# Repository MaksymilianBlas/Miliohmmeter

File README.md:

# Miliohmmeter
Miliohmmeter project, inspired by video on Learn Electronics Repair channel.
This is an adaptation of a project that has been shown on Learn Electronics Repair channel, link to original video:
https://www.youtube.com/watch?v=Sz1CqJltWEY
I wanted to replace the bulky PCB (that was designed by someone and posted on PCBway projects page) with my own design, with SMD parts and better layout. The project was made in KiCad.
Additionally, a linear power supply has been integrated onto the PCB.
The PCBA with a suitable transformer has been placed in a small project case, with banana sockets and a 5-digit display.
Along the way, there have been some issues caused by counterfit OP07 op-amps from aliexpress.
The weakpoint of the project are the home-made poor-mans kelvin connection probes, because the tip is soldered together and is neither sharp enough or resistant to oxidation enough to guarantee a long problem-free and pleasant usage. The leads were not updated due to high cost and lost interest.

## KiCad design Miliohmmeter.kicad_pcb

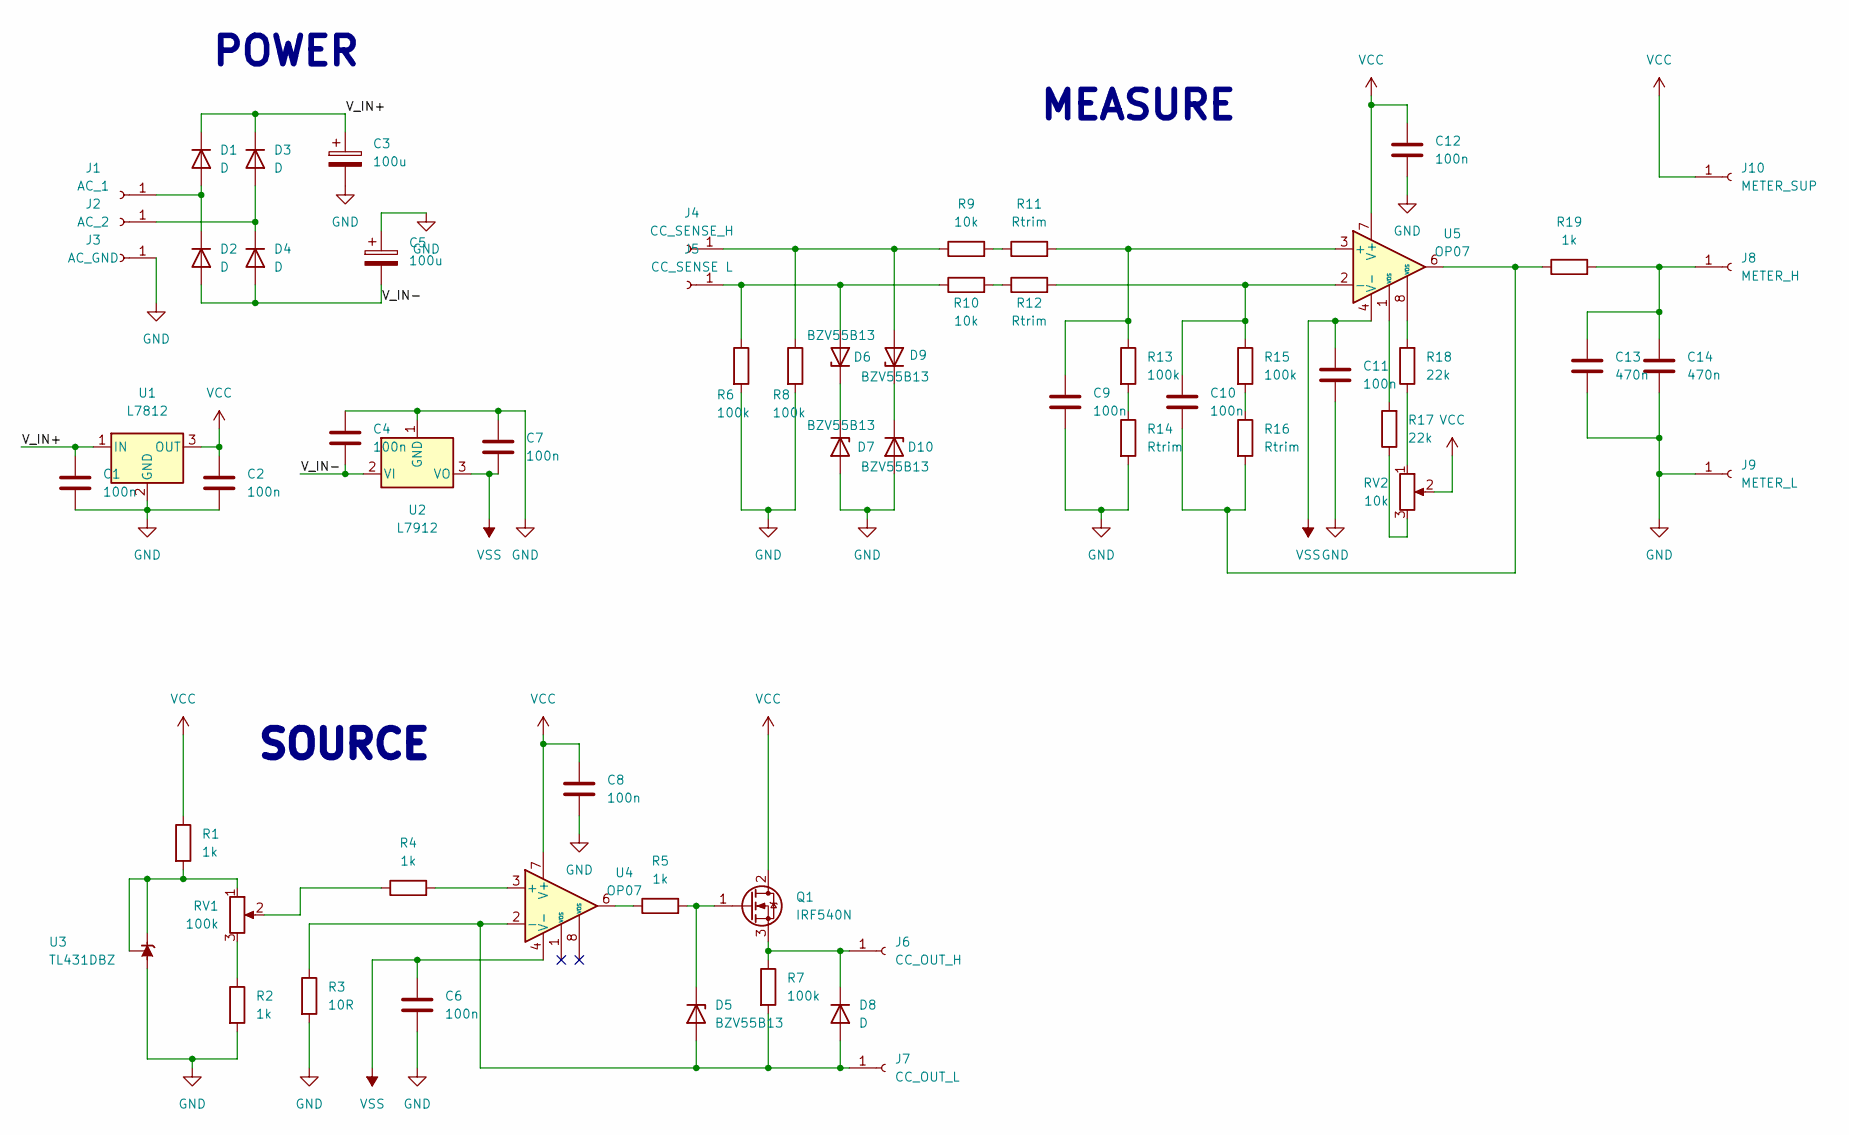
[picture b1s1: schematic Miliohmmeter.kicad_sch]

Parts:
C1, C2, C4, C6, C7, C8, C9, C10, C11, C12: 100n; C_0603_1608Metric_Pad1.08x0.95mm_HandSolder
C3, C5: 100u; CAP_EEETP1J102M
C13, C14: 470n; C_0805_2012Metric_Pad1.18x1.45mm_HandSolder
D1, D2, D3, D4, D8: D; D_SMA_Handsoldering
D5, D6, D7, D9, D10: BZV55B13; D_MiniMELF
J1: AC_1; SolderWire-0.75sqmm_1x01_D1.25mm_OD3.5mm
J2: AC_2; SolderWire-0.75sqmm_1x01_D1.25mm_OD3.5mm
J3: AC_GND; SolderWire-0.75sqmm_1x01_D1.25mm_OD3.5mm
J4: CC_SENSE_H; SolderWire-0.75sqmm_1x01_D1.25mm_OD3.5mm
J5: CC_SENSE L; SolderWire-0.75sqmm_1x01_D1.25mm_OD3.5mm
J6: CC_OUT_H; SolderWire-0.75sqmm_1x01_D1.25mm_OD3.5mm
J7: CC_OUT_L; SolderWire-0.75sqmm_1x01_D1.25mm_OD3.5mm
J8: METER_H; SolderWire-0.75sqmm_1x01_D1.25mm_OD3.5mm
J9: METER_L; SolderWire-0.75sqmm_1x01_D1.25mm_OD3.5mm
J10: METER_SUP; SolderWire-0.75sqmm_1x01_D1.25mm_OD3.5mm
Q1: IRF540N; TO-252-2
R1, R2, R4, R5, R19: 1k; R_0603_1608Metric_Pad0.98x0.95mm_HandSolder
R3: 10R; R_0805_2012Metric_Pad1.20x1.40mm_HandSolder
R6, R7, R8, R13, R15: 100k; R_0603_1608Metric_Pad0.98x0.95mm_HandSolder
R9, R10: 10k; R_0603_1608Metric_Pad0.98x0.95mm_HandSolder
R11, R12, R14, R16: Rtrim; R_0603_1608Metric_Pad0.98x0.95mm_HandSolder
R17, R18: 22k; R_0603_1608Metric_Pad0.98x0.95mm_HandSolder
RV1: 100k; Potentiometer_Bourns_3296W_Vertical
RV2: 10k; Potentiometer_Bourns_3296W_Vertical
U1: L7812; TO-252-2
U2: L7912; TO-252-2
U3: TL431DBZ; SOT-23_Handsoldering
U4, U5: OP07; SOIC-8_3.9x4.9mm_P1.27mm

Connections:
/V_IN+: C1.1, C3.1, D1.1 (K), D3.1 (K), U1.1 (IN)
/V_IN-: C4.2, C5.2, D2.2 (A), D4.2 (A), U2.2 (VI)
GND: C1.2, C2.2, C3.2, C4.1, C5.1, C6.2, C7.1, C8.2, C9.2, C11.2, C12.2, C13.2, C14.2, D7.2 (A), D10.2 (A), J3.1, J9.1, R2.2, R3.2, R6.2, R8.2, R14.2, U1.2 (GND), U2.1 (GND), U3.3 (A)
unnamed: C9.1, R11.2, R13.1, U5.3 (+)
unnamed: C10.1, R12.2, R15.1, U5.2 (-)
unnamed: C10.2, R16.2, R19.1, U5.6
unnamed: C13.1, C14.1, J8.1, R19.2
unnamed: D1.2 (A), D2.1 (K), J1.1
unnamed: D3.2 (A), D4.1 (K), J2.1
unnamed: D5.1 (K), Q1.1 (G), R5.2
unnamed: D5.2 (A), D8.2 (A), J7.1, R3.1, R7.2, U4.2 (-)
unnamed: D6.1 (K), D7.1 (K)
unnamed: D6.2 (A), J5.1, R6.1, R10.1
unnamed: D8.1 (K), J6.1, Q1.3 (S), R7.1
unnamed: D9.2 (A), J4.1, R8.1, R9.1
unnamed: D9.1 (K), D10.1 (K)
unnamed: R1.2, RV1.1, U3.1 (K), U3.2 (REF)
unnamed: R2.1, RV1.3
unnamed: R4.1, RV1.2
unnamed: R4.2, U4.3 (+)
unnamed: R5.1, U4.6
unnamed: R10.2, R12.1
unnamed: R9.2, R11.1
unnamed: R13.2, R14.1
unnamed: R15.2, R16.1
unnamed: R17.1, RV2.3
unnamed: R17.2, U5.1 (VOS)
unnamed: R18.1, RV2.1
unnamed: R18.2, U5.8 (VOS)
VCC: C2.1, C8.1, C12.1, J10.1, Q1.2 (D), R1.1, RV2.2, U1.3 (OUT), U4.7 (V+), U5.7 (V+)
VSS: C6.1, C7.2, C11.1, U2.3 (VO), U4.4 (V-), U5.4 (V-)

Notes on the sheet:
MEASURE
SOURCE
POWER

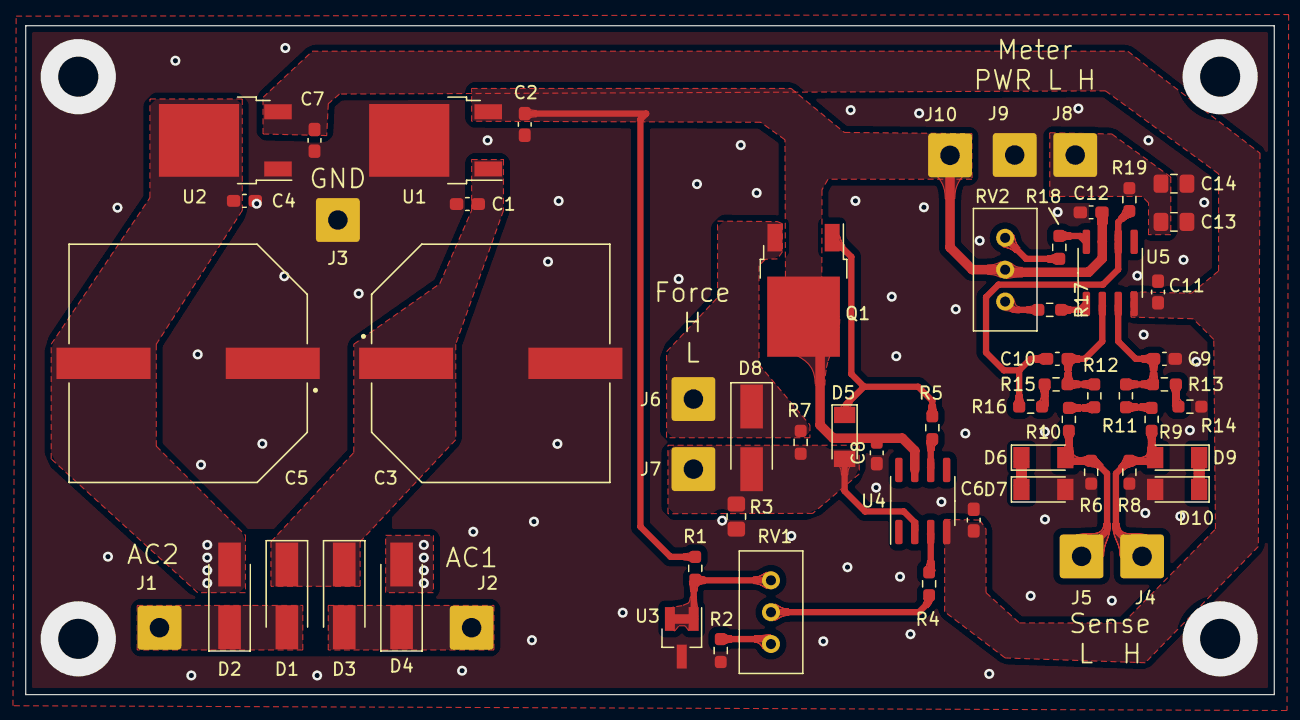
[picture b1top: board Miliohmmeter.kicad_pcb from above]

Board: 2 copper layers, 99.6 x 53.3 mm, 61 parts (0 on the bottom side), 31 nets.

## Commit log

2025-03-03 Add files via upload
    Added KiCad project files and .stl model for a transformator holder for the project case.
2025-03-03 Update README.md
    Added note about KiCad.
